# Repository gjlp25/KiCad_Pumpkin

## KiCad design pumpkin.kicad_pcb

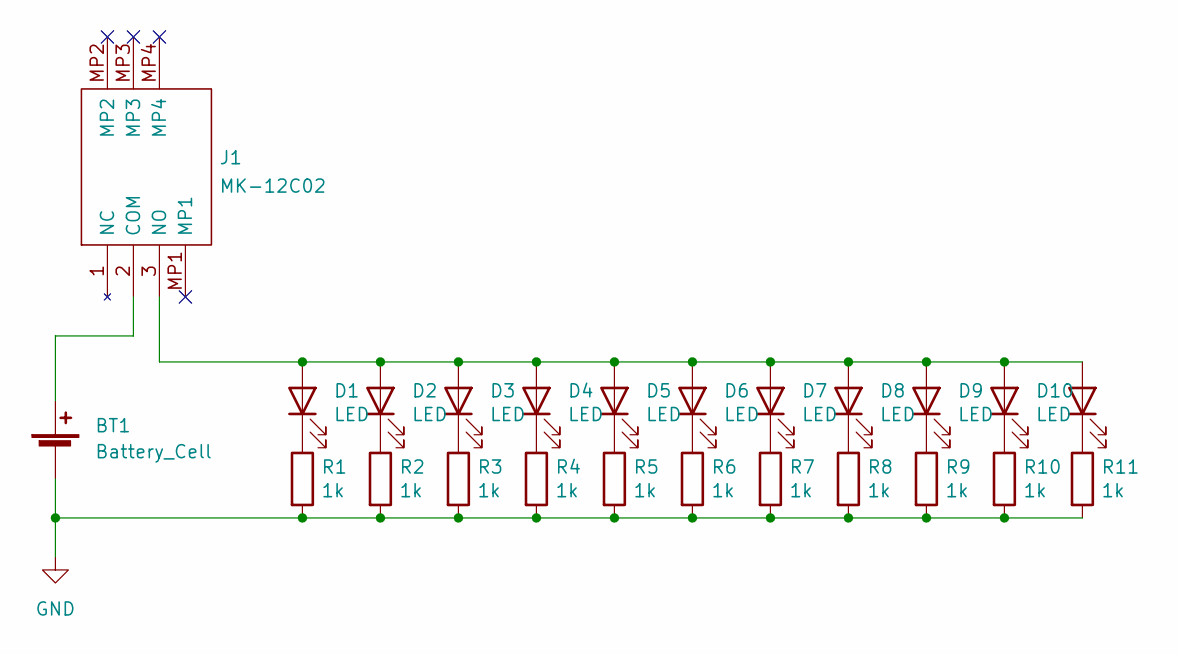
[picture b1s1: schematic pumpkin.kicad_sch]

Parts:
BT1: Battery_Cell; BatteryHolder_LINX_BAT-HLD-012-SMT
D1, D2, D3, D4, D5, D6, D7, D8, D9, D10, D11: LED; LED_0805_2012Metric_Pad1.15x1.40mm_HandSolder
J1: MK-12C02; MK12C02; Manufacturer_Part_Number MK-12C02
R1, R2, R3, R4, R5, R6, R7, R8, R9, R10, R11: 1k; R_0805_2012Metric_Pad1.20x1.40mm_HandSolder

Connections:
GND: BT1.2 (-), R1.2, R2.2, R3.2, R4.2, R5.2, R6.2, R7.2, R8.2, R9.2, R10.2, R11.2
unnamed: BT1.1 (+), J1.2 (COM)
unnamed: D1.2 (A), D2.2 (A), D3.2 (A), D4.2 (A), D5.2 (A), D6.2 (A), D7.2 (A), D8.2 (A), D9.2 (A), D10.2 (A), D11.2 (A), J1.3 (NO)
unnamed: D1.1 (K), R1.1
unnamed: D2.1 (K), R2.1
unnamed: D3.1 (K), R3.1
unnamed: D4.1 (K), R4.1
unnamed: D5.1 (K), R5.1
unnamed: D6.1 (K), R6.1
unnamed: D7.1 (K), R7.1
unnamed: D8.1 (K), R8.1
unnamed: D9.1 (K), R9.1
unnamed: D10.1 (K), R10.1
unnamed: D11.1 (K), R11.1

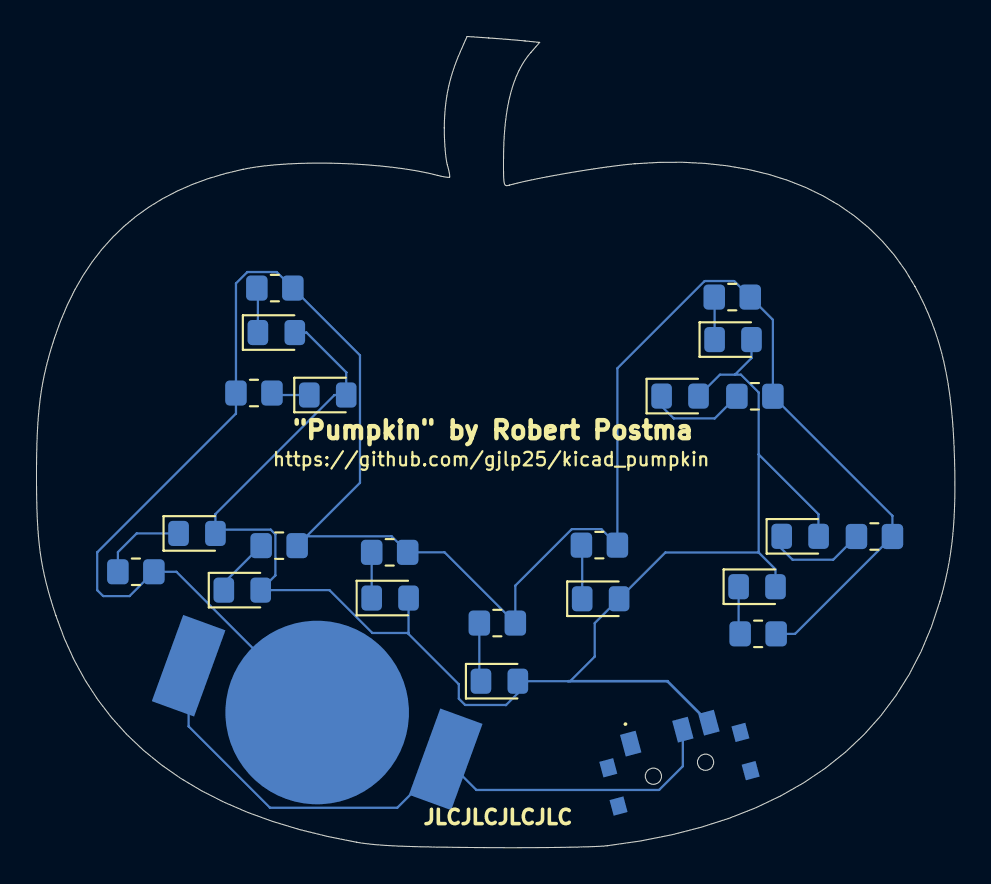
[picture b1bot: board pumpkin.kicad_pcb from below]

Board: 4 copper layers, 51.0 x 45.1 mm, 24 parts (24 on the bottom side), 14 nets.

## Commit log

2023-08-23 changed cr2032 to cr1225
2023-08-23 latest
2023-08-23 finished tracks
2023-08-23 shizzle
2023-08-23 added gerbers
